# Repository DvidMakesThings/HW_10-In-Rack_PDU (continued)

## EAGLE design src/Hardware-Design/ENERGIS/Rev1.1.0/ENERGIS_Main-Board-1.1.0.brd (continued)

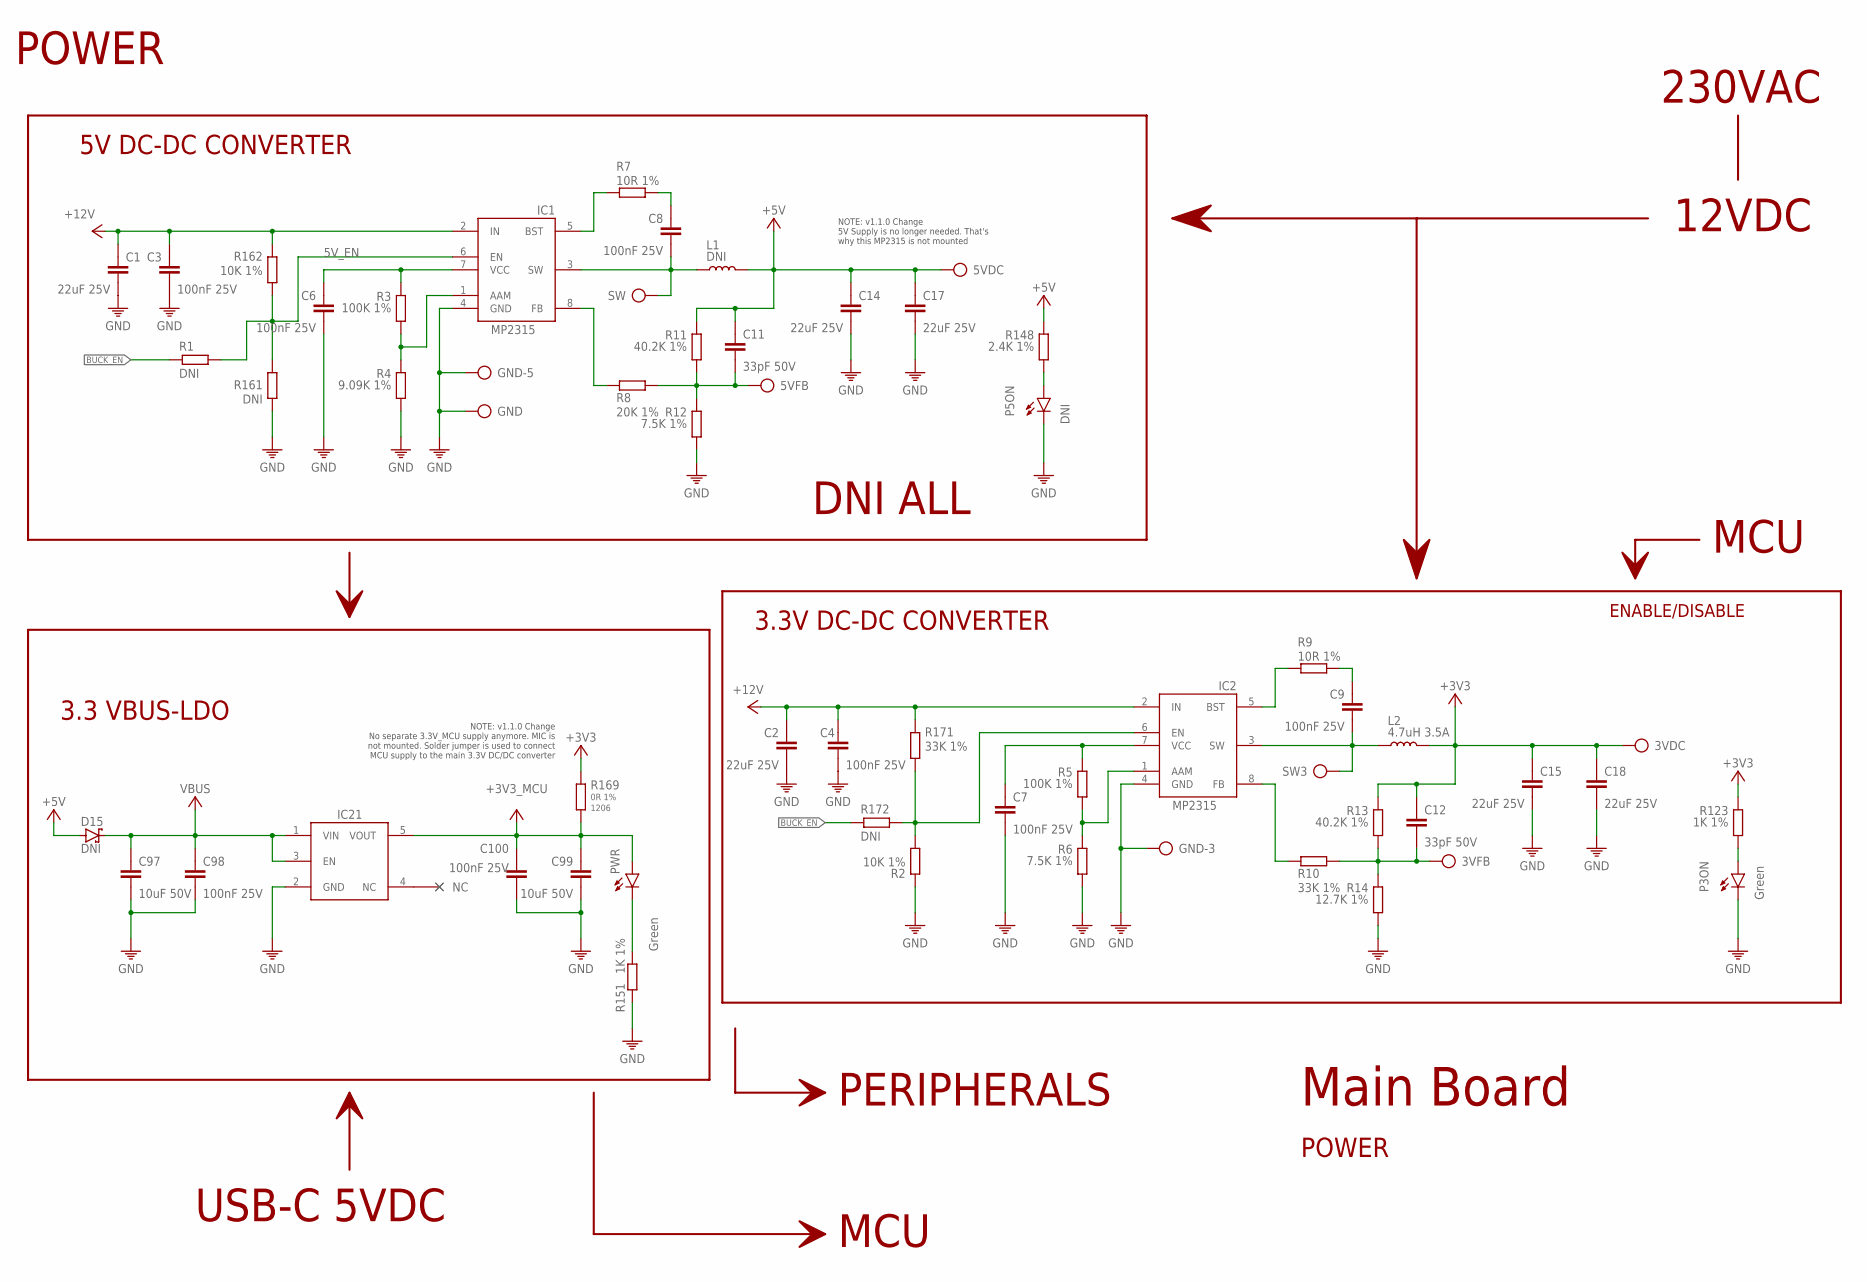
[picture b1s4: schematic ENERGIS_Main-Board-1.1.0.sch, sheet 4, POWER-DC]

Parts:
3VDC, 3VFB, 5VDC, 5VFB: DNI; TP-ROUND
C1, C2, C14, C15, C17, C18: 22uF 25V; 1206
C3, C4, C6, C7, C8, C9: 100nF 25V; 0402
C11, C12: 33pF 50V; 0402
C97, C99: 10uF 50V; 0805
C98, C100: 100nF 25V; 0201
D15: DNI; SMA/DO-214AC
GND: DNI; TP-ROUND
GND-3, GND-5: DNI; TP-ROUND
IC1: DNI; SOT65P280X110-8N
IC2: MP2315GJ-Z; SOT65P280X110-8N
IC21: MIC5504-3.3YM5; SOT23-5
L1: DNI; SRR5228A
L2: 4.7uH 3.5A; SRR5228A
P3ON: Green; LED-0603
P5ON: DNI; LED-0603
PWR: Green; LED-0603
R1, R161, R172: DNI; 0402
R2, R162: 10K 1%; 0402
R3, R5: 100K 1%; 0402
R4: 9.09K 1%; 0402
R6, R12: 7.5K 1%; 0402
R7, R9: 10R 1%; 0402
R8: 20K 1%; 0402
R10, R171: 33K 1%; 0402
R11, R13: 40.2K 1%; 0402
R14: 12.7K 1%; 0402
R123, R151: 1K 1%; 0402
R148: 2.4K 1%; 0402
R169: 0R 1%; 1206
SW, SW3: DNI; TP-ROUND

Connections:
3V3_EN: IC2.6 (EN), R2.2, R171.1, R172.1
3VFB: 3VFB.TP, C12.2, R10.2, R13.2, R14.1
5VFB: 5VFB.TP, C11.2, R8.2, R11.2, R12.1
5V_EN: IC1.6 (EN), R1.1, R161.2, R162.1
+3V3: 3VDC.TP, C12.1, C15.1, C18.1, L2.2, R13.1, R123.1, R169.1; also elsewhere on the board
+3V3_MCU: C99.1, C100.1, IC21.5 (VOUT), PWR.A, R169.2; also elsewhere on the board
+5V: 5VDC.TP, C11.1, C14.1, C17.1, D15.A, L1.2, R11.1, R148.1; also elsewhere on the board
+12V: C1.1, C2.1, C3.1, C4.1, IC1.2 (IN), IC2.2 (IN), R162.2, R171.2; also elsewhere on the board
BUCK_EN: R1.2, R172.2; also elsewhere on the board
GND: C1.2, C2.2, C3.2, C4.2, C6.2, C7.2, C14.2, C15.2, C17.2, C18.2, C97.2, C98.2, C99.2, C100.2, GND.TP, GND-3.TP, GND-5.TP, IC1.4 (GND), IC2.4 (GND), IC21.2 (GND), P3ON.C, P5ON.C, R2.1, R4.2, R6.2, R12.2, R14.2, R151.1, R161.1; also elsewhere on the board
unnamed: P3ON.A, R123.2
unnamed: P5ON.A, R148.2
unnamed: IC1.5 (BST), R7.2
unnamed: IC1.8 (FB), R8.1
unnamed: C8.1, R7.1
unnamed: C6.1, IC1.7 (VCC), R3.1
unnamed: IC2.5 (BST), R9.2
unnamed: IC2.8 (FB), R10.1
unnamed: C9.1, R9.1
unnamed: C7.1, IC2.7 (VCC), R5.1
unnamed: IC1.1 (AAM), R3.2, R4.1
unnamed: IC2.1 (AAM), R5.2, R6.1
unnamed: PWR.C, R151.2
SW3: C9.2, IC2.3 (SW), L2.1, SW3.TP
SW5: C8.2, IC1.3 (SW), L1.1, SW.TP
VBUS: C97.1, C98.1, D15.C, IC21.1 (VIN), IC21.3 (EN); also elsewhere on the board

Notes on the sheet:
5V DC-DC CONVERTER
3.3V DC-DC CONVERTER
3.3 VBUS-LDO
230VAC
12VDC
USB-C 5VDC
PERIPHERALS
MCU
ENABLE/DISABLE
Main Board
POWER
NOTE: v1.1.0 Change 5V Supply is no longer needed. That's why this MP2315 is not mounted
NOTE: v1.1.0 Change No separate 3.3V_MCU supply anymore. MIC is not mounted. Solder jumper is used to connect MCU supply to the main 3.3V DC/DC converter
DNI ALL

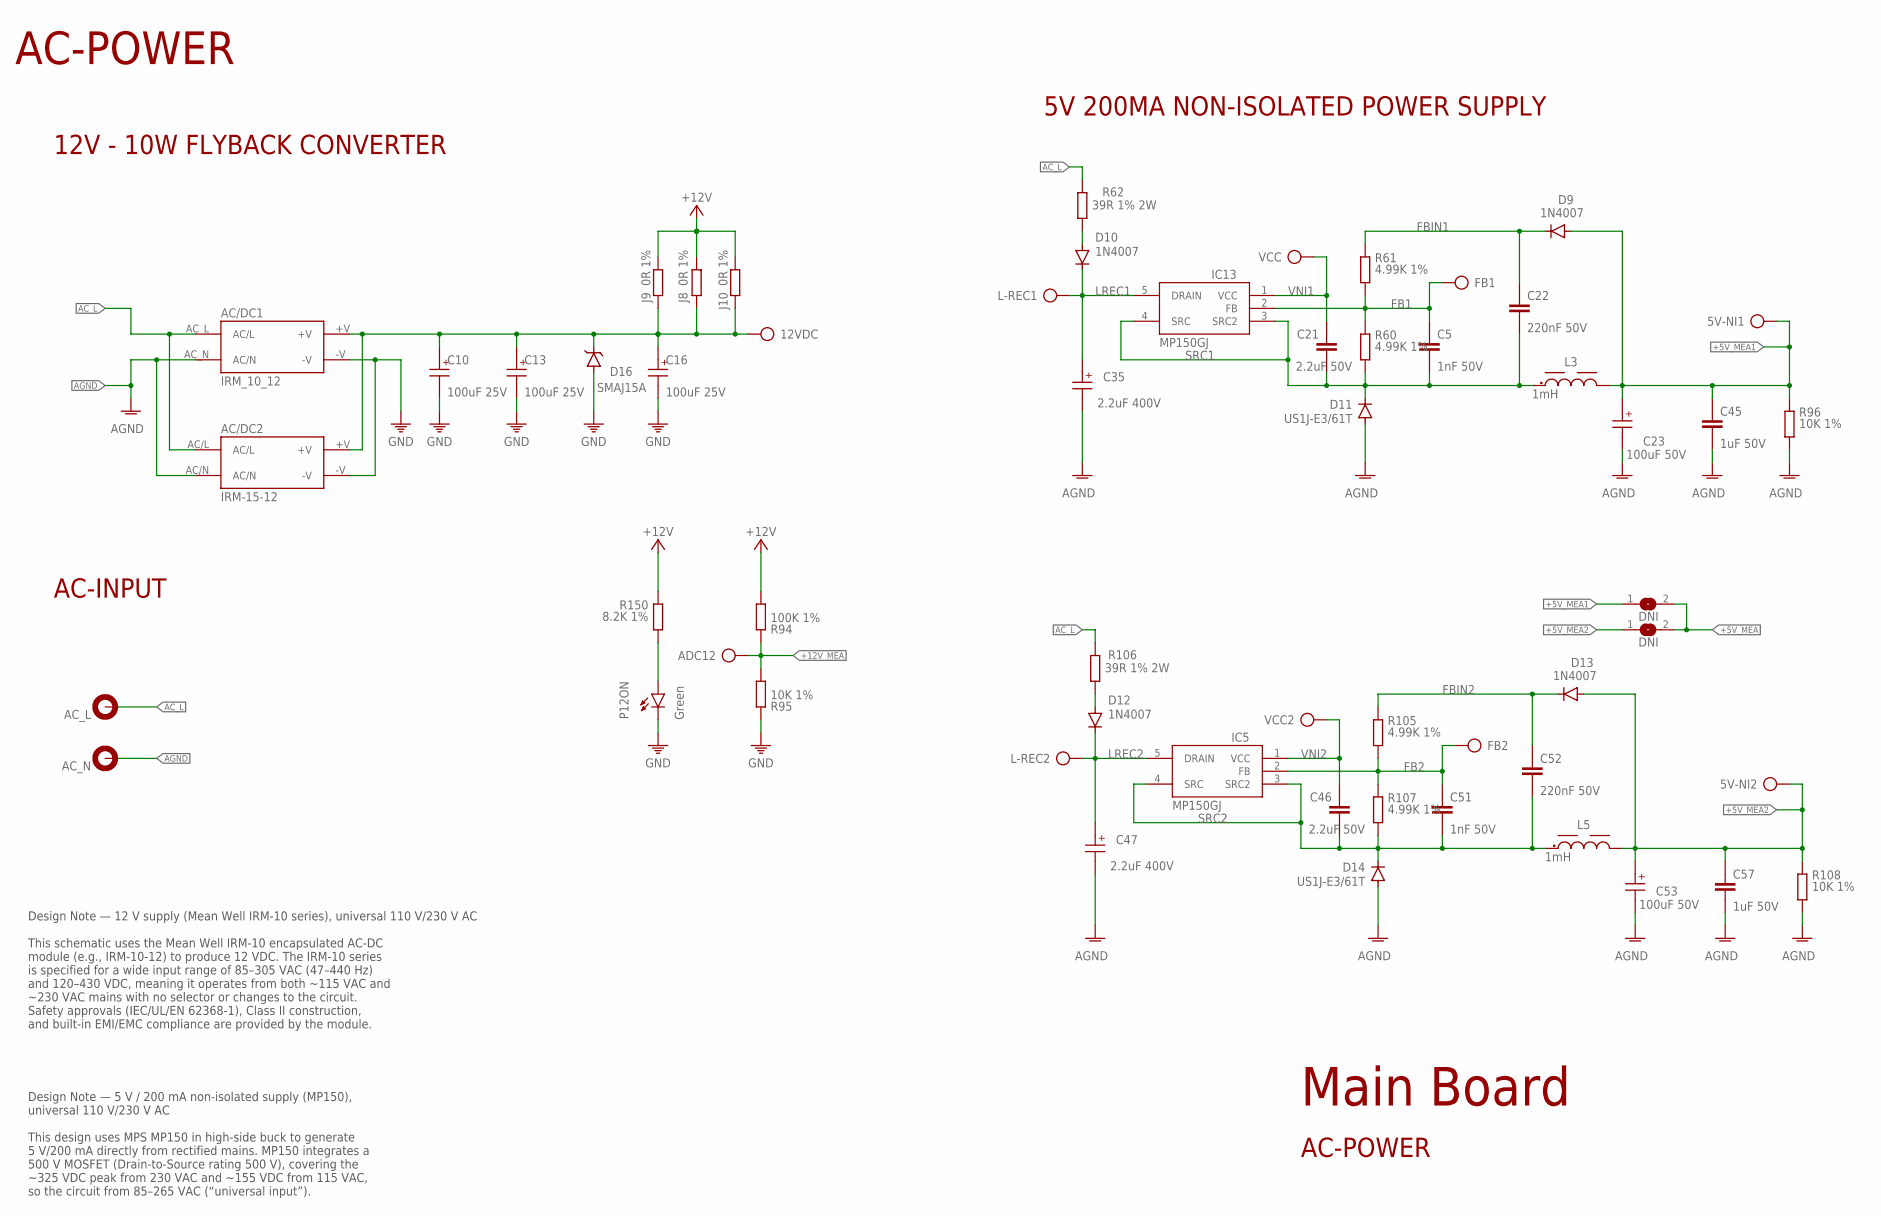
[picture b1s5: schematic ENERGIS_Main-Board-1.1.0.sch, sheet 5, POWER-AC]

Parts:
5V-NI1, 5V-NI2, 12VDC: DNI; TP-ROUND
AC/DC1: IRM_10_12
AC/DC2: IRM-15-12; IRM_15_12
AC_L: FASTON-1217861-1; 1217861-1
AC_N: FASTON-1217861-1; 1217861-1
ADC12: DNI; TP-ROUND
C5, C51: 1nF 50V; 0603
C10, C13, C16: 100uF 25V; 6.3X7.7(DXL)
C21, C46: 2.2uF 50V; 0603
C22, C52: 220nF 50V; 0805
C23, C53: 100uF 50V; 6.3X7.7(DXL)
C35, C47: 2.2uF 400V; 6.3X7.7(DXL)
C45, C57: 1uF 50V; 0805
D9, D10, D12, D13: 1N4007; SMA/DO-214AC
D11, D14: US1J-E3/61T; SMA/DO-214AC
D16: SMAJ15A; SMA/DO-214AC
FB1, FB2: DNI; TP-ROUND
IC5, IC13: MP150GJ; SOT23-5
J2, J7: DNI; SJ
J8, J9, J10: 0R 1%; 0805
L3, L5: 1mH; L-6.6X6.6
L-REC1, L-REC2: DNI; TP-ROUND
P12ON: Green; LED-0603
R60, R61, R105, R107: 4.99K 1%; 0603
R62, R106: 39R 1% 2W; 2512
R94: 100K 1%; 0402
R95: 10K 1%; 0402
R96, R108: 10K 1%; 0805
R150: 8.2K 1%; 0402
VCC, VCC2: DNI; TP-ROUND

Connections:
12VRAW: 12VDC.TP, AC/DC1.+V, AC/DC2.+V, C10.1 (+), C13.1 (+), C16.1 (+), D16.C, J8.2, J9.2, J10.2
+5V_MEA: J2.2, J7.2; also elsewhere on the board
+5V_MEA1: 5V-NI1.TP, C23.1 (+), C45.2, D9.A, J2.1, L3.2, R96.1
+5V_MEA2: 5V-NI2.TP, C53.1 (+), C57.2, D13.A, J7.1, L5.2, R108.1
+12V: J8.1, J9.1, J10.1, R94.2, R150.1; also elsewhere on the board
+12V_MEA: ADC12.TP, R94.1, R95.2; also elsewhere on the board
AC_L: AC/DC1.AC_L (AC/L), AC/DC2.AC/L, AC_L.1, AC_L.2, R62.1, R106.1; also elsewhere on the board
AGND: AC/DC1.AC_N (AC/N), AC/DC2.AC/N, AC_N.1, AC_N.2, C23.2 (-), C35.2 (-), C45.1, C47.2 (-), C53.2 (-), C57.1, D11.A, D14.A, R96.2, R108.2; also elsewhere on the board
FB1: C5.2, FB1.TP, IC13.2 (FB), R60.1, R61.2
FB2: C51.2, FB2.TP, IC5.2 (FB), R105.2, R107.1
FBIN1: C22.2, D9.C, R61.1
FBIN2: C52.2, D13.C, R105.1
GND: AC/DC1.-V, AC/DC2.-V, C10.2 (-), C13.2 (-), C16.2 (-), D16.A, P12ON.C, R95.1; also elsewhere on the board
LREC1: C35.1 (+), D10.C, IC13.5 (DRAIN), L-REC1.TP
LREC2: C47.1 (+), D12.C, IC5.5 (DRAIN), L-REC2.TP
unnamed: D10.A, R62.2
unnamed: P12ON.A, R150.2
unnamed: D12.A, R106.2
SRC1: C5.1, C21.1, C22.1, D11.C, IC13.3 (SRC2), IC13.4 (SRC), L3.1, R60.2
SRC2: C46.1, C51.1, C52.1, D14.C, IC5.3 (SRC2), IC5.4 (SRC), L5.1, R107.2
VNI1: C21.2, IC13.1 (VCC), VCC.TP
VNI2: C46.2, IC5.1 (VCC), VCC2.TP

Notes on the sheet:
AC-POWER
5V 200MA NON-ISOLATED POWER SUPPLY
AC-INPUT
Design Note — 5 V / 200 mA non-isolated supply (MP150), universal 110 V/230 V AC This design uses MPS MP150 in high-side buck to generate 5 V/200 mA directly from rectified mains. MP150 integrates a 500 V MOSFET (Drain-to-Source rating 500 V), covering the ~325 VDC peak from 230 VAC and ~155 VDC fr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
Design Note — 12 V supply (Mean Well IRM-10 series), universal 110 V/230 V AC This schematic uses the Mean Well IRM-10 encapsulated AC-DC module (e.g., IRM-10-12) to produce 12 VDC. The IRM-10 series is specified for a wide input range of 85–305 VAC (47–440 Hz) and 120–430 VDC, meaning it operates 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
Main Board
12V - 10W FLYBACK CONVERTER

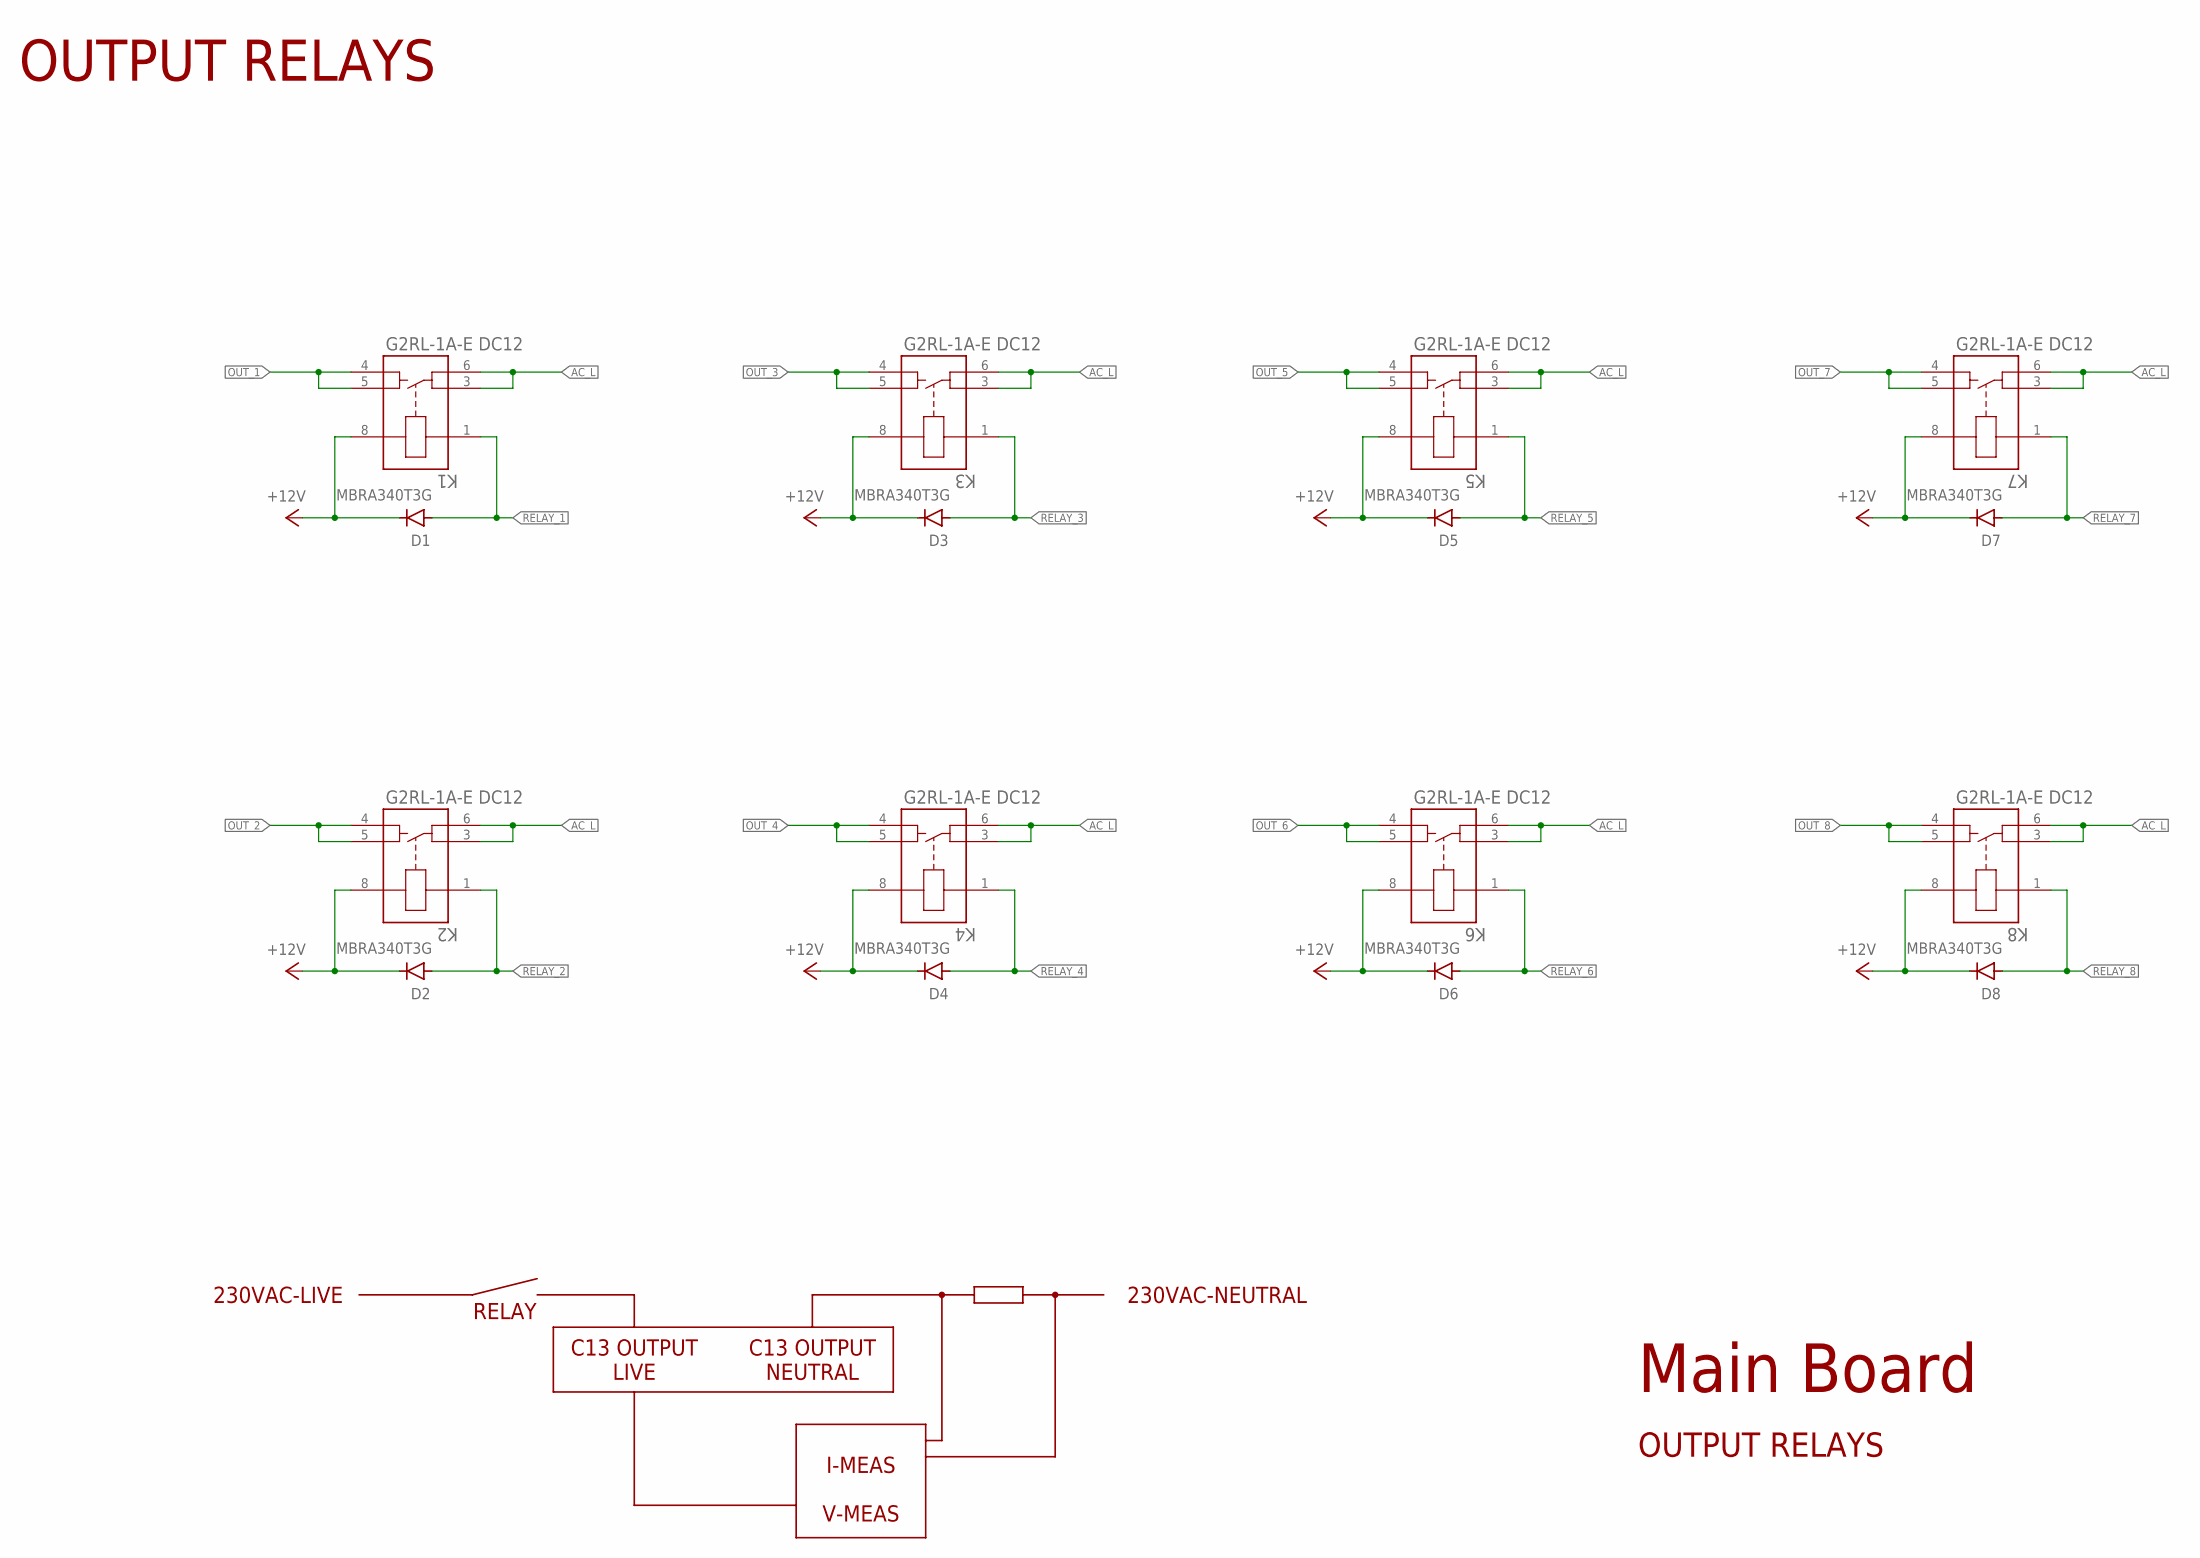
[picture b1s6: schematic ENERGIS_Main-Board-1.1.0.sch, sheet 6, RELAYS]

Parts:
D1, D2, D3, D4, D5, D6, D7, D8: MBRA340T3G; SMA/DO-214AC
K1, K2, K3, K4, K5, K6, K7, K8: G2RL-1A-E DC12; RELAY_G2RL-1A-E_DC5_OMR

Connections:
+12V: D1.C, D2.C, D3.C, D4.C, D5.C, D6.C, D7.C, D8.C, K1.8, K2.8, K3.8, K4.8, K5.8, K6.8, K7.8, K8.8; also elsewhere on the board
AC_L: K1.3, K1.6, K2.3, K2.6, K3.3, K3.6, K4.3, K4.6, K5.3, K5.6, K6.3, K6.6, K7.3, K7.6, K8.3, K8.6; also elsewhere on the board
OUT_1: K1.4, K1.5; also elsewhere on the board
OUT_2: K2.4, K2.5; also elsewhere on the board
OUT_3: K3.4, K3.5; also elsewhere on the board
OUT_4: K4.4, K4.5; also elsewhere on the board
OUT_5: K5.4, K5.5; also elsewhere on the board
OUT_6: K6.4, K6.5; also elsewhere on the board
OUT_7: K7.4, K7.5; also elsewhere on the board
OUT_8: K8.4, K8.5; also elsewhere on the board
RELAY_1: D1.A, K1.1; also elsewhere on the board
RELAY_2: D2.A, K2.1; also elsewhere on the board
RELAY_3: D3.A, K3.1; also elsewhere on the board
RELAY_4: D4.A, K4.1; also elsewhere on the board
RELAY_5: D5.A, K5.1; also elsewhere on the board
RELAY_6: D6.A, K6.1; also elsewhere on the board
RELAY_7: D7.A, K7.1; also elsewhere on the board
RELAY_8: D8.A, K8.1; also elsewhere on the board

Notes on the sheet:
OUTPUT RELAYS
230VAC-LIVE
C13 OUTPUT NEUTRAL
C13 OUTPUT LIVE
RELAY
230VAC-NEUTRAL
I-MEAS V-MEAS
Main Board

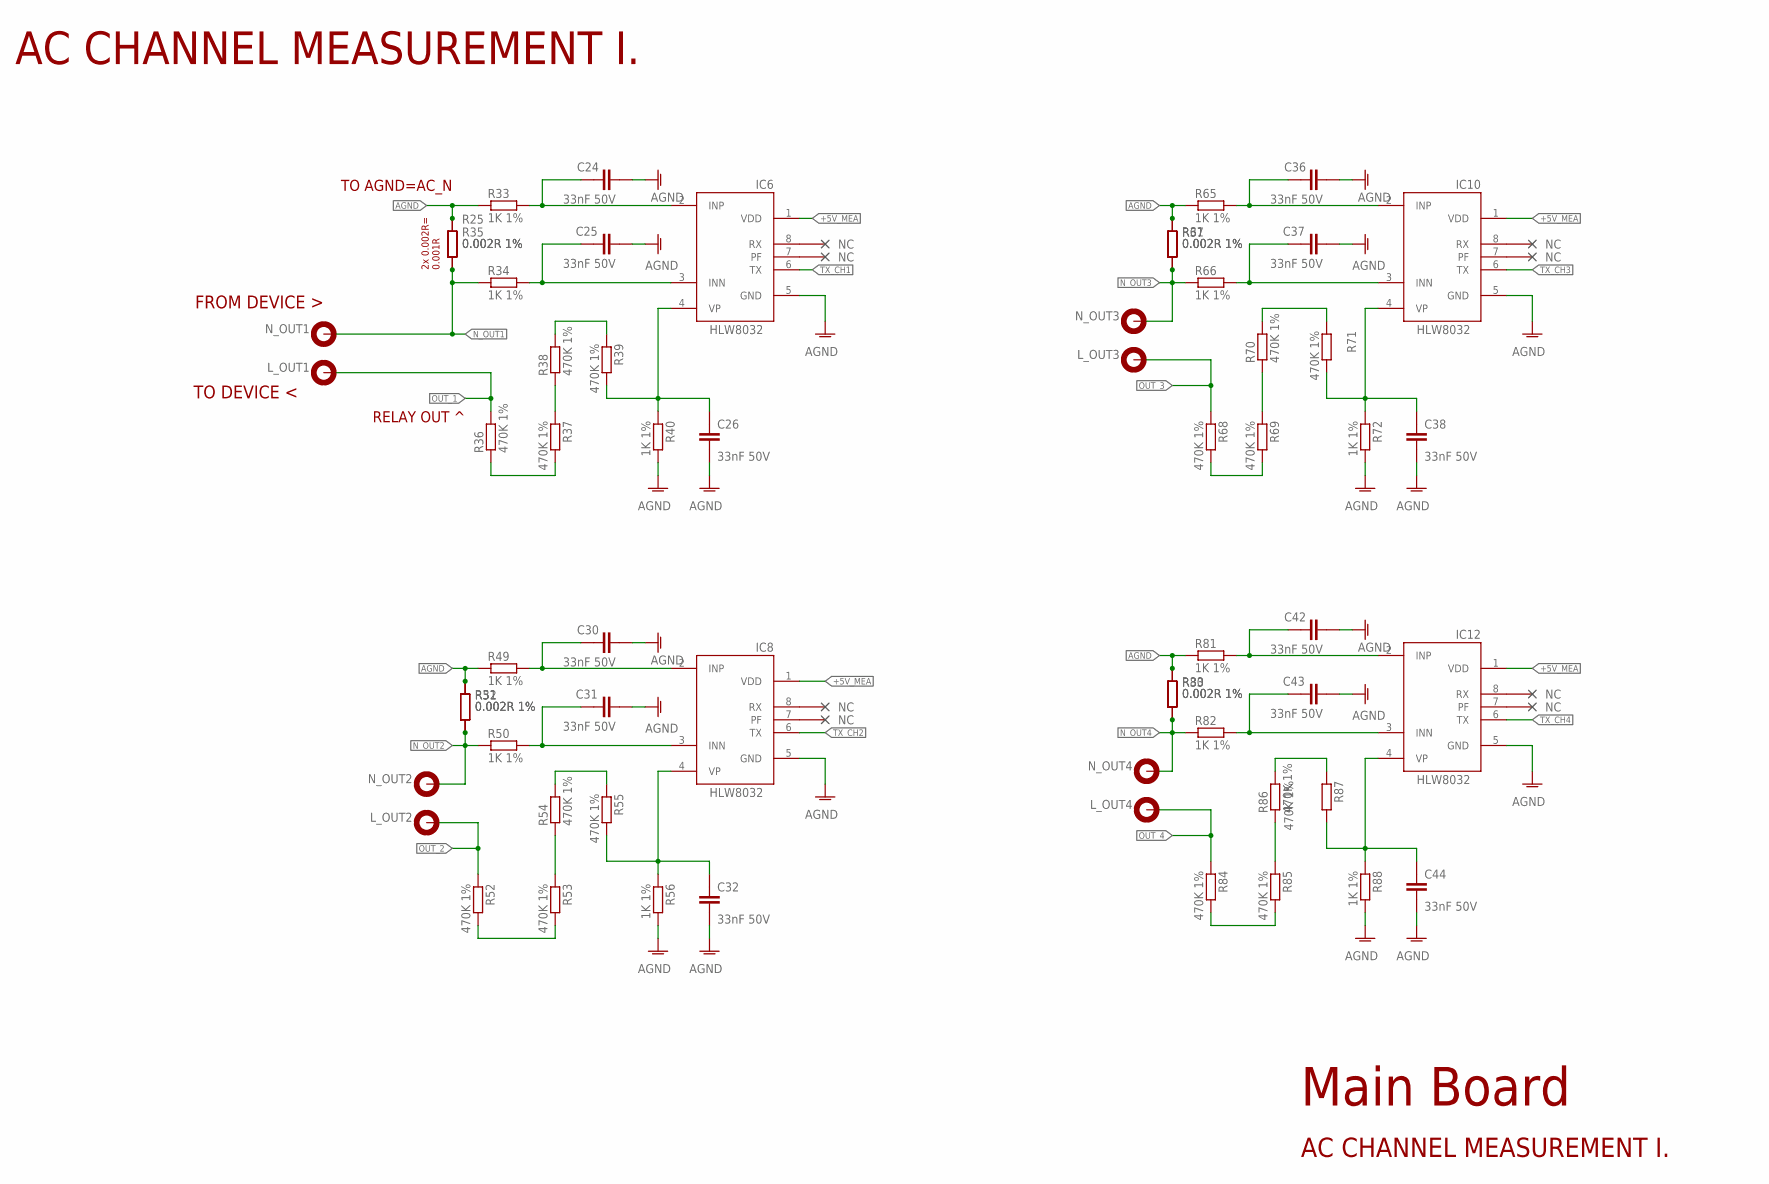
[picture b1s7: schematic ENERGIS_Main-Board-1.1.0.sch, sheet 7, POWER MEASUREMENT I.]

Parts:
C24, C25, C26, C30, C31, C32, C36, C37, C38, C42, C43, C44: 33nF 50V; 0805
IC6, IC8, IC10, IC12: HLW8032; SO8
L_OUT1, L_OUT2, L_OUT3, L_OUT4: FASTON-1217861-1; 1217861-1
N_OUT1, N_OUT2, N_OUT3, N_OUT4: FASTON-1217861-1; 1217861-1
R25, R30, R31, R32, R35, R51, R67, R83: 0.002R 1%; 2512
R33, R34, R40, R49, R50, R56, R65, R66, R72, R81, R82, R88: 1K 1%; 0805
R36, R37, R38, R39, R52, R53, R54, R55, R68, R69, R70, R71, R84, R85, R86, R87: 470K 1%; 0805

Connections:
+5V_MEA: IC6.1 (VDD), IC8.1 (VDD), IC10.1 (VDD), IC12.1 (VDD); also elsewhere on the board
AGND: C24.2, C25.2, C26.2, C30.2, C31.2, C32.2, C36.2, C37.2, C38.2, C42.2, C43.2, C44.2, IC6.5 (GND), IC8.5 (GND), IC10.5 (GND), IC12.5 (GND), R25.2, R30.2, R31.2, R32.2, R33.1, R35.2, R40.2, R49.1, R51.2, R56.2, R65.1, R67.2, R72.2, R81.1, R83.2, R88.2; also elsewhere on the board
unnamed: C24.1, IC6.2 (INP), R33.2
unnamed: C25.1, IC6.3 (INN), R34.2
unnamed: R38.2, R39.1
unnamed: R52.2, R53.2
unnamed: R37.1, R38.1
unnamed: C26.1, IC6.4 (VP), R39.2, R40.1
unnamed: R53.1, R54.1
unnamed: R54.2, R55.1
unnamed: R68.2, R69.2
unnamed: C30.1, IC8.2 (INP), R49.2
unnamed: C31.1, IC8.3 (INN), R50.2
unnamed: R69.1, R70.1
unnamed: R70.2, R71.1
unnamed: R84.2, R85.2
unnamed: C32.1, IC8.4 (VP), R55.2, R56.1
unnamed: C36.1, IC10.2 (INP), R65.2
unnamed: C37.1, IC10.3 (INN), R66.2
unnamed: R85.1, R86.1
unnamed: R86.2, R87.1
unnamed: C38.1, IC10.4 (VP), R71.2, R72.1
unnamed: C42.1, IC12.2 (INP), R81.2
unnamed: C43.1, IC12.3 (INN), R82.2
unnamed: C44.1, IC12.4 (VP), R87.2, R88.1
unnamed: R36.1, R37.2
N_OUT1: N_OUT1.1, N_OUT1.2, R25.1, R34.1, R35.1
N_OUT2: N_OUT2.1, N_OUT2.2, R32.1, R50.1, R51.1
N_OUT3: N_OUT3.1, N_OUT3.2, R31.1, R66.1, R67.1
N_OUT4: N_OUT4.1, N_OUT4.2, R30.1, R82.1, R83.1
OUT_1: L_OUT1.1, L_OUT1.2, R36.2; also elsewhere on the board
OUT_2: L_OUT2.1, L_OUT2.2, R52.1; also elsewhere on the board
OUT_3: L_OUT3.1, L_OUT3.2, R68.1; also elsewhere on the board
OUT_4: L_OUT4.1, L_OUT4.2, R84.1; also elsewhere on the board
TX_CH1: IC6.6 (TX); also elsewhere on the board
TX_CH2: IC8.6 (TX); also elsewhere on the board
TX_CH3: IC10.6 (TX); also elsewhere on the board
TX_CH4: IC12.6 (TX); also elsewhere on the board

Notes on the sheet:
AC CHANNEL MEASUREMENT I.
TO DEVICE <
FROM DEVICE >
2x 0.002R= 0.001R
TO AGND=AC_N
RELAY OUT ^
Main Board

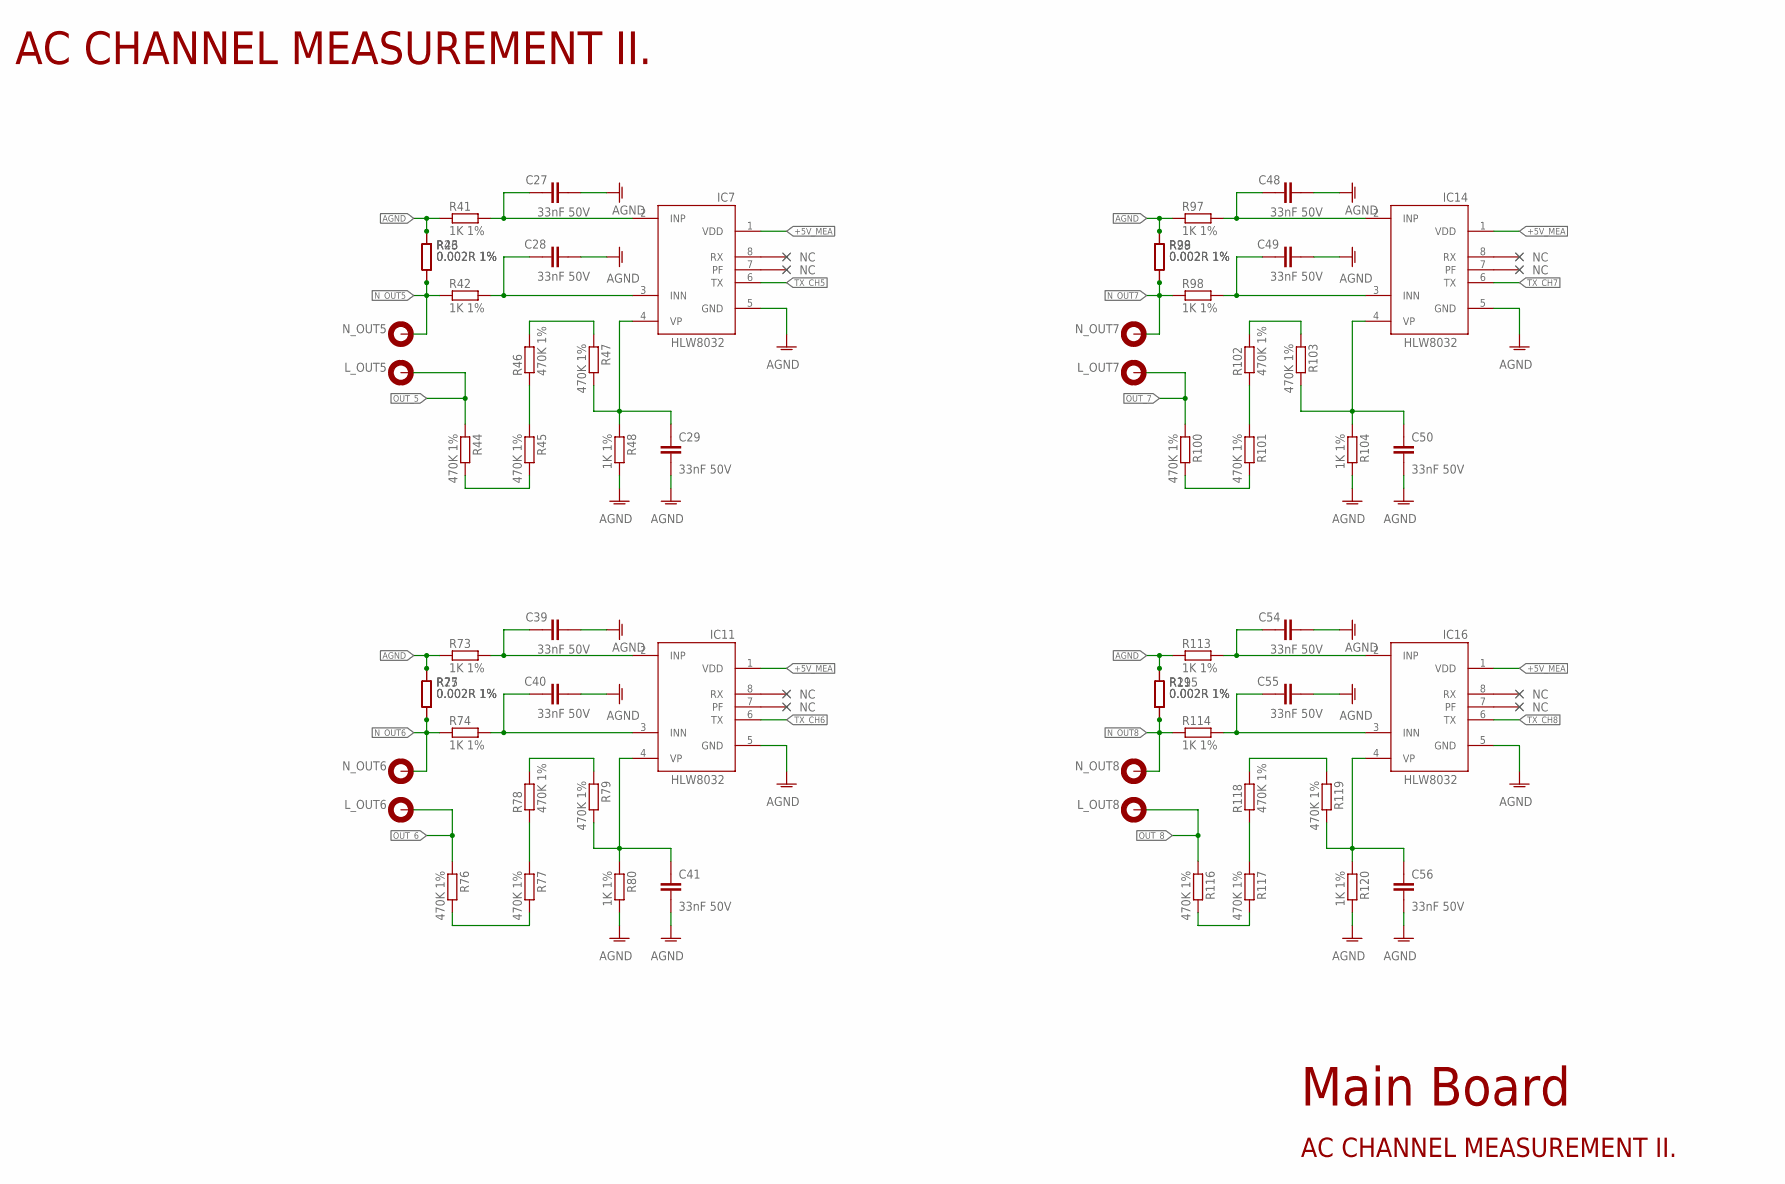
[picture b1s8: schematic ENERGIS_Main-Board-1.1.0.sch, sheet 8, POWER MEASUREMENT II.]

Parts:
C27, C28, C29, C39, C40, C41, C48, C49, C50, C54, C55, C56: 33nF 50V; 0805
IC7, IC11, IC14, IC16: HLW8032; SO8
L_OUT5, L_OUT6, L_OUT7, L_OUT8: FASTON-1217861-1; 1217861-1
N_OUT5, N_OUT6, N_OUT7, N_OUT8: FASTON-1217861-1; 1217861-1
R26, R27, R28, R29, R43, R75, R99, R115: 0.002R 1%; 2512
R41, R42, R48, R73, R74, R80, R97, R98, R104, R113, R114, R120: 1K 1%; 0805
R44, R45, R46, R47, R76, R77, R78, R79, R100, R101, R102, R103, R116, R117, R118, R119: 470K 1%; 0805

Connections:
+5V_MEA: IC7.1 (VDD), IC11.1 (VDD), IC14.1 (VDD), IC16.1 (VDD); also elsewhere on the board
AGND: C27.2, C28.2, C29.2, C39.2, C40.2, C41.2, C48.2, C49.2, C50.2, C54.2, C55.2, C56.2, IC7.5 (GND), IC11.5 (GND), IC14.5 (GND), IC16.5 (GND), R26.2, R27.2, R28.2, R29.2, R41.1, R43.2, R48.2, R73.1, R75.2, R80.2, R97.1, R99.2, R104.2, R113.1, R115.2, R120.2; also elsewhere on the board
unnamed: C27.1, IC7.2 (INP), R41.2
unnamed: C28.1, IC7.3 (INN), R42.2
unnamed: C29.1, IC7.4 (VP), R47.2, R48.1
unnamed: R44.2, R45.2
unnamed: C39.1, IC11.2 (INP), R73.2
unnamed: C40.1, IC11.3 (INN), R74.2
unnamed: R45.1, R46.1
unnamed: R46.2, R47.1
unnamed: R76.2, R77.2
unnamed: C41.1, IC11.4 (VP), R79.2, R80.1
unnamed: R77.1, R78.1
unnamed: R78.2, R79.1
unnamed: R100.2, R101.2
unnamed: C48.1, IC14.2 (INP), R97.2
unnamed: C49.1, IC14.3 (INN), R98.2
unnamed: R101.1, R102.1
unnamed: R102.2, R103.1
unnamed: R116.2, R117.2
unnamed: C50.1, IC14.4 (VP), R103.2, R104.1
unnamed: C54.1, IC16.2 (INP), R113.2
unnamed: C55.1, IC16.3 (INN), R114.2
unnamed: R117.1, R118.1
unnamed: R118.2, R119.1
unnamed: C56.1, IC16.4 (VP), R119.2, R120.1
N_OUT5: N_OUT5.1, N_OUT5.2, R26.1, R42.1, R43.1
N_OUT6: N_OUT6.1, N_OUT6.2, R27.1, R74.1, R75.1
N_OUT7: N_OUT7.1, N_OUT7.2, R28.1, R98.1, R99.1
N_OUT8: N_OUT8.1, N_OUT8.2, R29.1, R114.1, R115.1
OUT_5: L_OUT5.1, L_OUT5.2, R44.1; also elsewhere on the board
OUT_6: L_OUT6.1, L_OUT6.2, R76.1; also elsewhere on the board
OUT_7: L_OUT7.1, L_OUT7.2, R100.1; also elsewhere on the board
OUT_8: L_OUT8.1, L_OUT8.2, R116.1; also elsewhere on the board
TX_CH5: IC7.6 (TX); also elsewhere on the board
TX_CH6: IC11.6 (TX); also elsewhere on the board
TX_CH7: IC14.6 (TX); also elsewhere on the board
TX_CH8: IC16.6 (TX); also elsewhere on the board

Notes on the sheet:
AC CHANNEL MEASUREMENT II.
Main Board

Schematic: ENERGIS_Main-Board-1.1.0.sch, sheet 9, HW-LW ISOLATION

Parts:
C106, C107, C108, C109, C110, C111, C112, C113: 1nF 25V; 0201
OPT1, OPT2: ACPL-247-500E; SO16
R59, R153, R154, R155, R156, R157, R158, R159: 1K 1%; 0201
R63, R64: 1K 1%; _0603X4-1206
R89, R90: 10K 1%; _0603X4-1206

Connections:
+3V3: R89.A2 (8), R89.B2 (7), R89.C2 (6), R89.D2 (5), R90.A2 (8), R90.B2 (7), R90.C2 (6), R90.D2 (5); also elsewhere on the board
+5V_MEA: R63.A1 (1), R63.B1 (2), R63.C1 (3), R63.D1 (4), R64.A1 (1), R64.B1 (2), R64.C1 (3), R64.D1 (4); also elsewhere on the board
AGND: C106.2, C107.2, C108.2, C109.2, C110.2, C111.2, C112.2, C113.2; also elsewhere on the board
GND: OPT1.9, OPT1.11, OPT1.13, OPT1.15, OPT2.9, OPT2.11, OPT2.13, OPT2.15; also elsewhere on the board
TX1_LP: C109.1, OPT1.8, R155.2
TX1_PU: OPT1.7, R63.D2 (5)
TX2_LP: C108.1, OPT1.6, R154.2
TX2_PU: OPT1.5, R63.C2 (6)
TX3_LP: C107.1, OPT1.4, R153.2
TX3_PU: OPT1.3, R63.B2 (7)
TX4_LP: C106.1, OPT1.2, R59.2
TX4_PU: OPT1.1, R63.A2 (8)
TX5_LP: C110.1, OPT2.2, R156.2
TX5_PU: OPT2.1, R64.A2 (8)
TX6_LP: C111.1, OPT2.4, R157.2
TX6_PU: OPT2.3, R64.B2 (7)
TX7_LP: C112.1, OPT2.6, R158.2
TX7_PU: OPT2.5, R64.C2 (6)
TX8_LP: C113.1, OPT2.8, R159.2
TX8_PU: OPT2.7, R64.D2 (5)
TX_CH1: R155.1; also elsewhere on the board
TX_CH2: R154.1; also elsewhere on the board
TX_CH3: R153.1; also elsewhere on the board
TX_CH4: R59.1; also elsewhere on the board
TX_CH5: R159.1; also elsewhere on the board
TX_CH6: R158.1; also elsewhere on the board
TX_CH7: R157.1; also elsewhere on the board
TX_CH8: R156.1; also elsewhere on the board
TX_MUX1: OPT1.10, R89.D1 (4); also elsewhere on the board
TX_MUX2: OPT1.12, R89.C1 (3); also elsewhere on the board
TX_MUX3: OPT1.14, R89.B1 (2); also elsewhere on the board
TX_MUX4: OPT1.16, R89.A1 (1); also elsewhere on the board
TX_MUX5: OPT2.10, R90.A1 (1); also elsewhere on the board
TX_MUX6: OPT2.12, R90.B1 (2); also elsewhere on the board
TX_MUX7: OPT2.14, R90.C1 (3); also elsewhere on the board
TX_MUX8: OPT2.16, R90.D1 (4); also elsewhere on the board

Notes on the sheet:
SERIAL OPTOISOLATOR
Main Board
NOTE: v1.1.0 Change TX_MUX5:8 was switched in 1.0.0. Due to software correction, it had no impact. Correct wiring order is now implemented from 1.1.0

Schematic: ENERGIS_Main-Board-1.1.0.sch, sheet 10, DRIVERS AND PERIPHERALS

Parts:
C19, C20, C33, C34: 100nF 25V; 0402
C103: 100nF 25V; 0201
DAT: Blue; LED-0603
IC3: ULN2803AFWG; SO18
IC4: MCP23017T-E/ML; QFN28[6X6]ML
IC9: SN74HC151PWR; TSSOP16
IC22: MCP6001RT-I/OT; SOT23-5
R17, R18, R19, R20, R21, R22, R23, R24: 0R 1%; 2512
R57, R91: 0R 1%; 0402
R58, R92: DNI; 0402
R93: 10K 1%; _0603X4-1206
R122: 1K 1%; 0402
REL0, REL1, REL2, REL3, REL4, REL5, REL6, REL7: DNI; TP-ROUND
RN1, RN2: 100K 1%; _0603X4-1206
UTX: DNI; TP-ROUND

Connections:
!TX_OUT: IC9.6 (!Y), IC22.3 (+IN), R92.1
+3V3: C19.1, C20.1, C33.1, C34.1, C103.1, IC4.5 (VDD), IC9.16 (VCC), IC22.2 (V+); also elsewhere on the board
+12V: IC3.10 (COM); also elsewhere on the board
GND: C19.2, C20.2, C33.2, C34.2, C103.2, DAT.C, IC3.9 (GND), IC4.6 (VSS), IC4.11 (A0), IC4.12 (A1), IC4.13 (A2), IC4.PAD (VSS), IC9.8 (GND), IC22.5 (V-), R93.A2 (8), R93.B2 (7), R93.C2 (6), R93.D2 (5), RN1.A1 (1), RN1.B1 (1), RN1.C1 (1), RN1.D1 (1), RN2.A1 (1), RN2.B1 (1), RN2.C1 (1), RN2.D1 (1); also elsewhere on the board
I2C1_SCL: IC4.8 (SCL); also elsewhere on the board
I2C1_SDA: IC4.9 (SDA); also elsewhere on the board
MCP_REL_RST: IC4.14 (!RESET); also elsewhere on the board
MUX_A: IC4.25 (IO2.0), IC9.11 (A), R93.D1 (4)
MUX_B: IC4.26 (IO2.1), IC9.10 (B), R93.C1 (3)
MUX_C: IC4.27 (IO2.2), IC9.9 (C), R93.B1 (2)
MUX_EN: IC4.28 (IO2.3), IC9.7 (!EN), R93.A1 (1)
unnamed: DAT.A, R122.2
unnamed: IC3.14 (5C), R21.1
unnamed: IC3.11 (8C), R24.1
unnamed: IC3.12 (7C), R23.1
unnamed: IC3.13 (6C), R22.1
unnamed: IC3.15 (4C), R20.1
unnamed: IC3.16 (3C), R19.1
unnamed: IC3.17 (2C), R18.1
unnamed: IC3.18 (1C), R17.1
RELAY_1: R24.2; also elsewhere on the board
RELAY_2: R23.2; also elsewhere on the board
RELAY_3: R22.2; also elsewhere on the board
RELAY_4: R21.2; also elsewhere on the board
RELAY_5: R20.2; also elsewhere on the board
RELAY_6: R19.2; also elsewhere on the board
RELAY_7: R18.2; also elsewhere on the board
RELAY_8: R17.2; also elsewhere on the board
REL_0: IC3.8 (8B), IC4.17 (IO1.0), REL0.TP, RN1.A2 (2)
REL_1: IC3.7 (7B), IC4.18 (IO1.1), REL1.TP, RN1.B2 (2)
REL_2: IC3.6 (6B), IC4.19 (IO1.2), REL2.TP, RN1.C2 (2)
REL_3: IC3.5 (5B), IC4.20 (IO1.3), REL3.TP, RN1.D2 (2)
REL_4: IC3.4 (4B), IC4.21 (IO1.4), REL4.TP, RN2.A2 (2)
REL_5: IC3.3 (3B), IC4.22 (IO1.5), REL5.TP, RN2.B2 (2)
REL_6: IC3.2 (2B), IC4.23 (IO1.6), REL6.TP, RN2.C2 (2)
REL_7: IC3.1 (1B), IC4.24 (IO1.7), REL7.TP, RN2.D2 (2)
TX_FB: IC22.1 (OUT), IC22.4 (-IN), R122.1
TX_MUX1: IC9.4 (D0); also elsewhere on the board
TX_MUX2: IC9.3 (D1); also elsewhere on the board
TX_MUX3: IC9.2 (D2); also elsewhere on the board
TX_MUX4: IC9.1 (D3); also elsewhere on the board
TX_MUX5: IC9.15 (D4); also elsewhere on the board
TX_MUX6: IC9.14 (D5); also elsewhere on the board
TX_MUX7: IC9.13 (D6); also elsewhere on the board
TX_MUX8: IC9.12 (D7); also elsewhere on the board
TX_OUT: IC9.5 (Y), R91.1
TX_OUTSEL: R57.1, R58.1, R91.2, R92.2, UTX.TP
UART0_RX: R58.2; also elsewhere on the board
UART0_TX: R57.2; also elsewhere on the board

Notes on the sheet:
ULN2803 RELAY DRIVER
IO DRIVER
SERIAL MUX
TX1 TX2 TX3 ...
OPTO
IN1 M IN2 U IN3 X ...
SELECTOR
SEL A/B/C
OUT
MCU RX
RELAY1
RELAY2
RELAY3 ...
DRIVER
AC-MEASUREMENT SIGNAL PATH
Main Board
